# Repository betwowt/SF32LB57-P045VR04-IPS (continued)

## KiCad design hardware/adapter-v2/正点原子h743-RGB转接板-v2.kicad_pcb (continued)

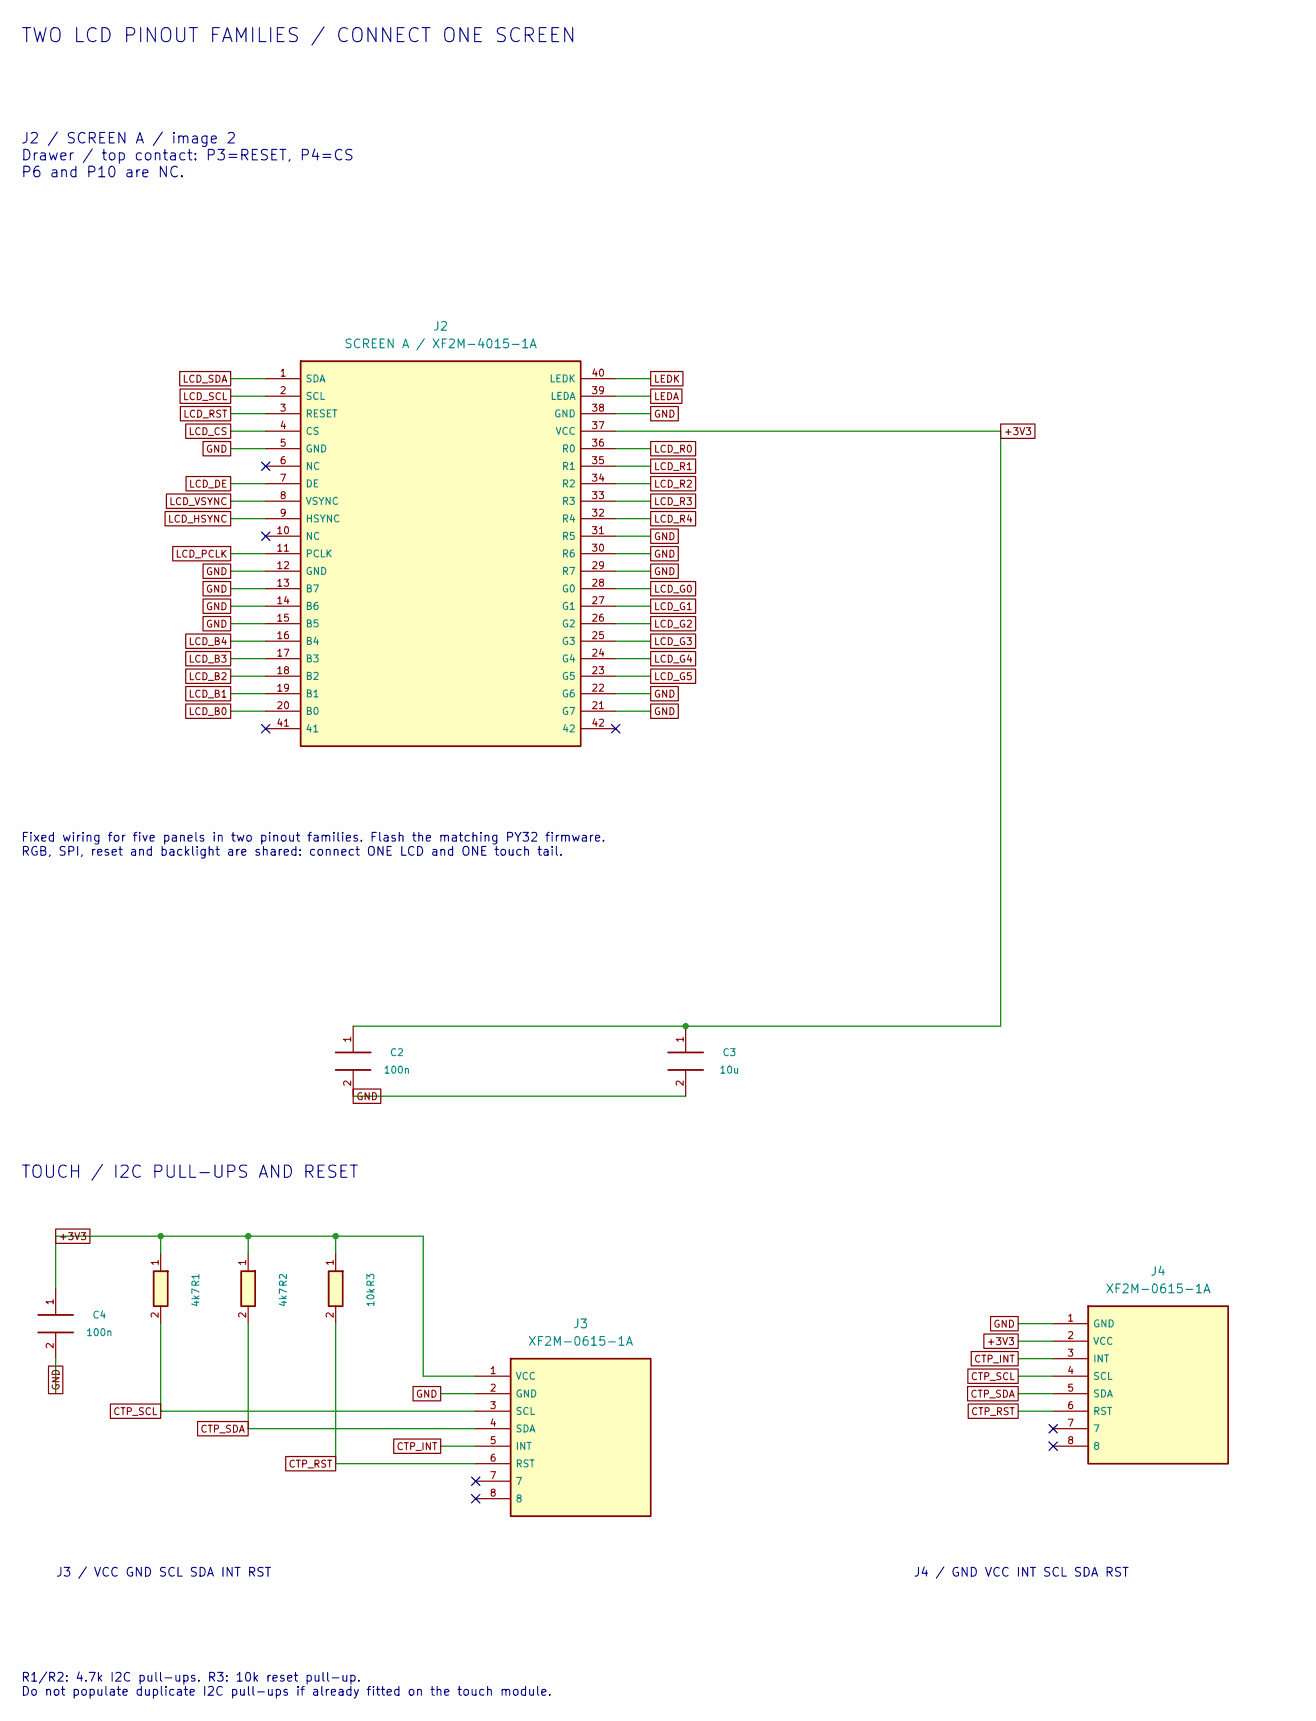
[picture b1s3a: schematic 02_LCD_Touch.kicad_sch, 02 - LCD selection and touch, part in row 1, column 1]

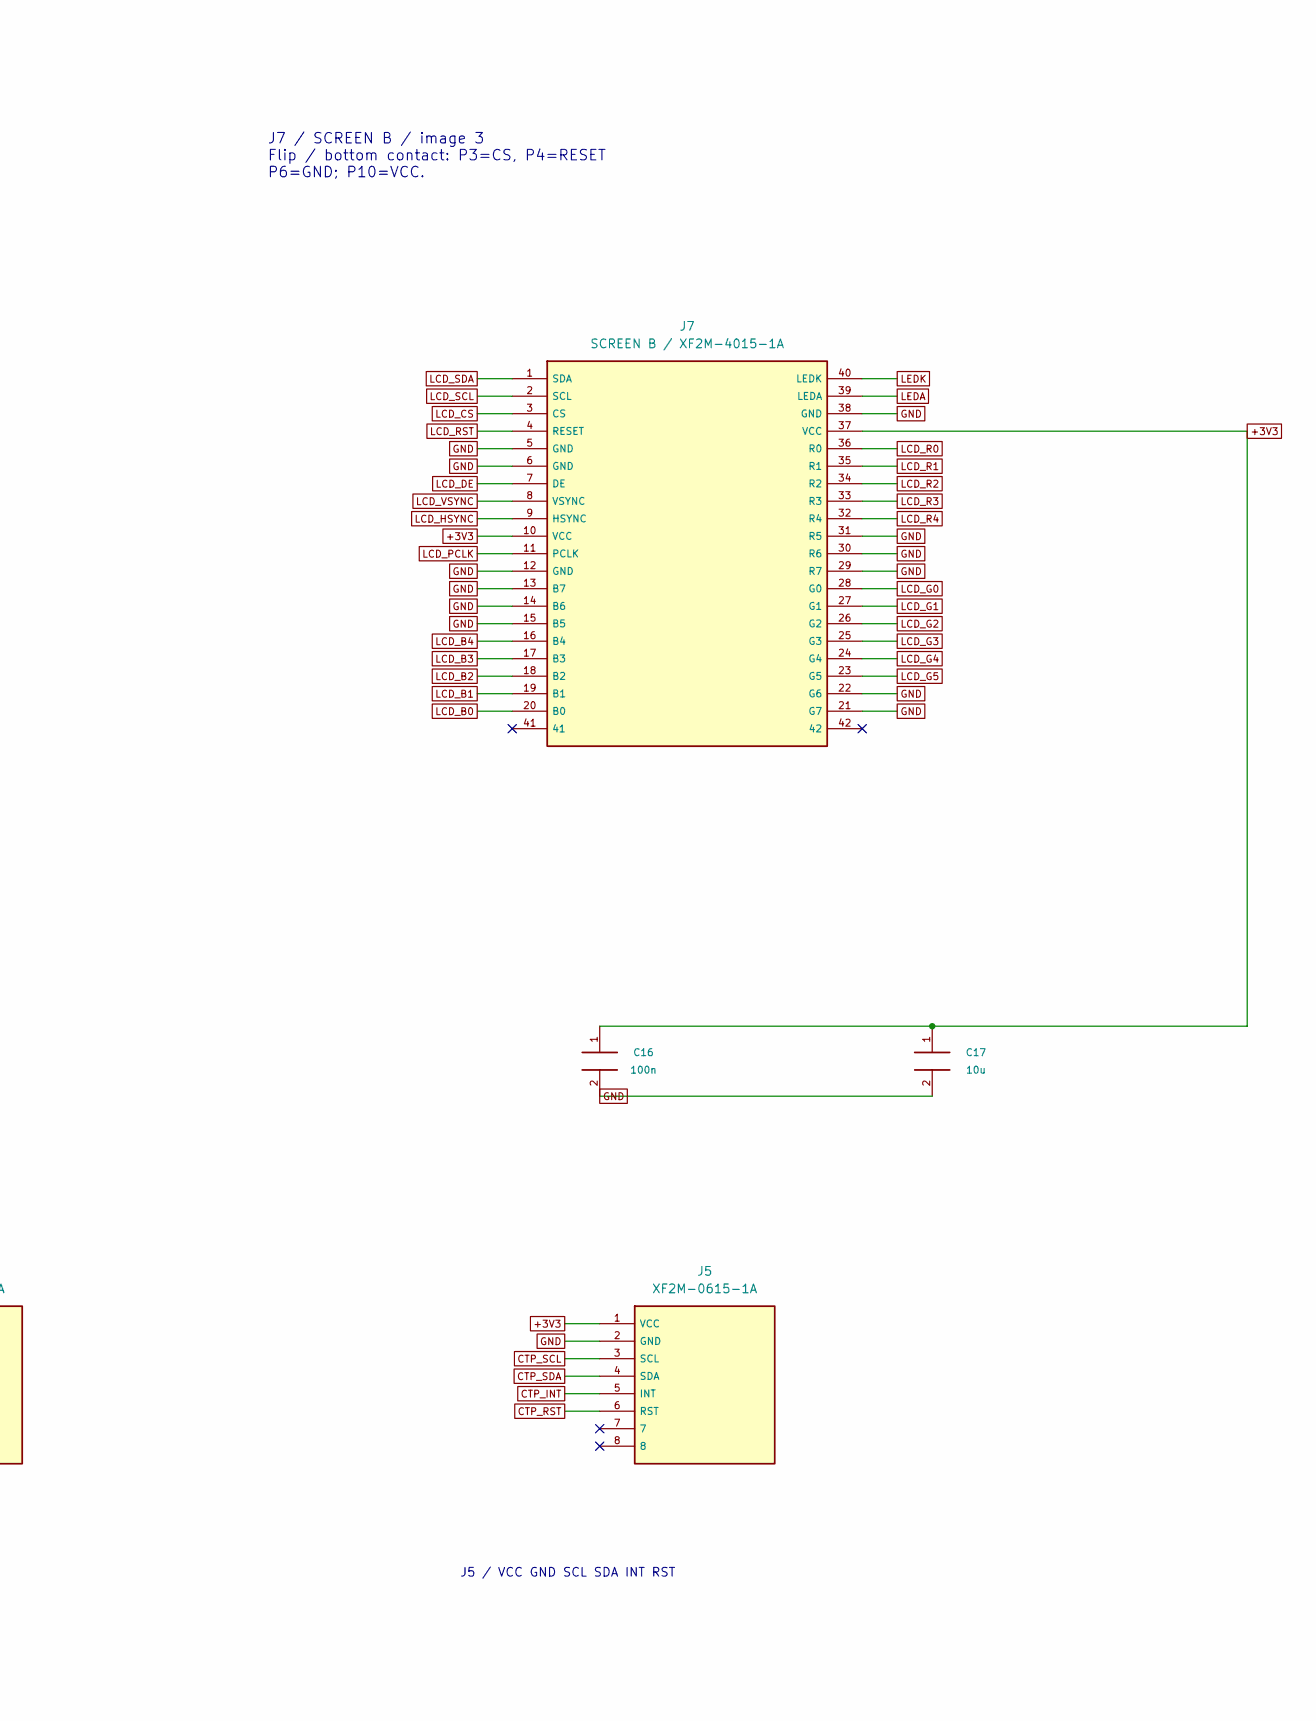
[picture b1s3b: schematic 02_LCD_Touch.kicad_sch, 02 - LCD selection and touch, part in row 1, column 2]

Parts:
C2, C4, C16: 100n; C_0603_1608Metric
C3, C17: 10u; C_0805_2012Metric
J2: SCREEN A / XF2M-4015-1A; FPC-SMD_P0.50-40P_LCS-SJ-H2.0
J3, J4, J5: XF2M-0615-1A; FPC-SMD_6P-P0.50_XUNPU_FPC-05F-6PH20
J7: SCREEN B / XF2M-4015-1A; FPC-SMD_AFC01-S40FCA-00
R1, R2: 4k7; R_0603_1608Metric
R3: 10k; R_0603_1608Metric

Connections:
+3V3: C2.1, C3.1, C4.1, C16.1, C17.1, J2.37 (VCC), J3.1 (VCC), J4.2 (VCC), J5.1 (VCC), J7.10 (VCC), J7.37 (VCC), R1.1, R2.1, R3.1; also elsewhere on the board
CTP_INT: J3.5 (INT), J4.3 (INT), J5.5 (INT); also elsewhere on the board
CTP_RST: J3.6 (RST), J4.6 (RST), J5.6 (RST), R3.2; also elsewhere on the board
CTP_SCL: J3.3 (SCL), J4.4 (SCL), J5.3 (SCL), R1.2; also elsewhere on the board
CTP_SDA: J3.4 (SDA), J4.5 (SDA), J5.4 (SDA), R2.2; also elsewhere on the board
GND: C2.2, C3.2, C4.2, C16.2, C17.2, J2.5 (GND), J2.12 (GND), J2.13 (B7), J2.14 (B6), J2.15 (B5), J2.21 (G7), J2.22 (G6), J2.29 (R7), J2.30 (R6), J2.31 (R5), J2.38 (GND), J3.2 (GND), J4.1 (GND), J5.2 (GND), J7.5 (GND), J7.6 (GND), J7.12 (GND), J7.13 (B7), J7.14 (B6), J7.15 (B5), J7.21 (G7), J7.22 (G6), J7.29 (R7), J7.30 (R6), J7.31 (R5), J7.38 (GND); also elsewhere on the board
LCD_B0: J2.20 (B0), J7.20 (B0); also elsewhere on the board
LCD_B1: J2.19 (B1), J7.19 (B1); also elsewhere on the board
LCD_B2: J2.18 (B2), J7.18 (B2); also elsewhere on the board
LCD_B3: J2.17 (B3), J7.17 (B3); also elsewhere on the board
LCD_B4: J2.16 (B4), J7.16 (B4); also elsewhere on the board
LCD_CS: J2.4 (CS), J7.3 (CS); also elsewhere on the board
LCD_DE: J2.7 (DE), J7.7 (DE); also elsewhere on the board
LCD_G0: J2.28 (G0), J7.28 (G0); also elsewhere on the board
LCD_G1: J2.27 (G1), J7.27 (G1); also elsewhere on the board
LCD_G2: J2.26 (G2), J7.26 (G2); also elsewhere on the board
LCD_G3: J2.25 (G3), J7.25 (G3); also elsewhere on the board
LCD_G4: J2.24 (G4), J7.24 (G4); also elsewhere on the board
LCD_G5: J2.23 (G5), J7.23 (G5); also elsewhere on the board
LCD_HSYNC: J2.9 (HSYNC), J7.9 (HSYNC); also elsewhere on the board
LCD_PCLK: J2.11 (PCLK), J7.11 (PCLK); also elsewhere on the board
LCD_R0: J2.36 (R0), J7.36 (R0); also elsewhere on the board
LCD_R1: J2.35 (R1), J7.35 (R1); also elsewhere on the board
LCD_R2: J2.34 (R2), J7.34 (R2); also elsewhere on the board
LCD_R3: J2.33 (R3), J7.33 (R3); also elsewhere on the board
LCD_R4: J2.32 (R4), J7.32 (R4); also elsewhere on the board
LCD_RST: J2.3 (RESET), J7.4 (RESET); also elsewhere on the board
LCD_SCL: J2.2 (SCL), J7.2 (SCL); also elsewhere on the board
LCD_SDA: J2.1 (SDA), J7.1 (SDA); also elsewhere on the board
LCD_VSYNC: J2.8 (VSYNC), J7.8 (VSYNC); also elsewhere on the board
LEDA: J2.39 (LEDA), J7.39 (LEDA); also elsewhere on the board
LEDK: J2.40 (LEDK), J7.40 (LEDK); also elsewhere on the board

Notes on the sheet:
J4 / GND VCC INT SCL SDA RST
J7 / SCREEN B / image 3 Flip / bottom contact: P3=CS, P4=RESET P6=GND; P10=VCC.
J3 / VCC GND SCL SDA INT RST
TWO LCD PINOUT FAMILIES / CONNECT ONE SCREEN
Fixed wiring for five panels in two pinout families. Flash the matching PY32 firmware. RGB, SPI, reset and backlight are shared: connect ONE LCD and ONE touch tail.
R1/R2: 4.7k I2C pull-ups. R3: 10k reset pull-up. Do not populate duplicate I2C pull-ups if already fitted on the touch module.
J2 / SCREEN A / image 2 Drawer / top contact: P3=RESET, P4=CS P6 and P10 are NC.
J5 / VCC GND SCL SDA INT RST
TOUCH / I2C PULL-UPS AND RESET

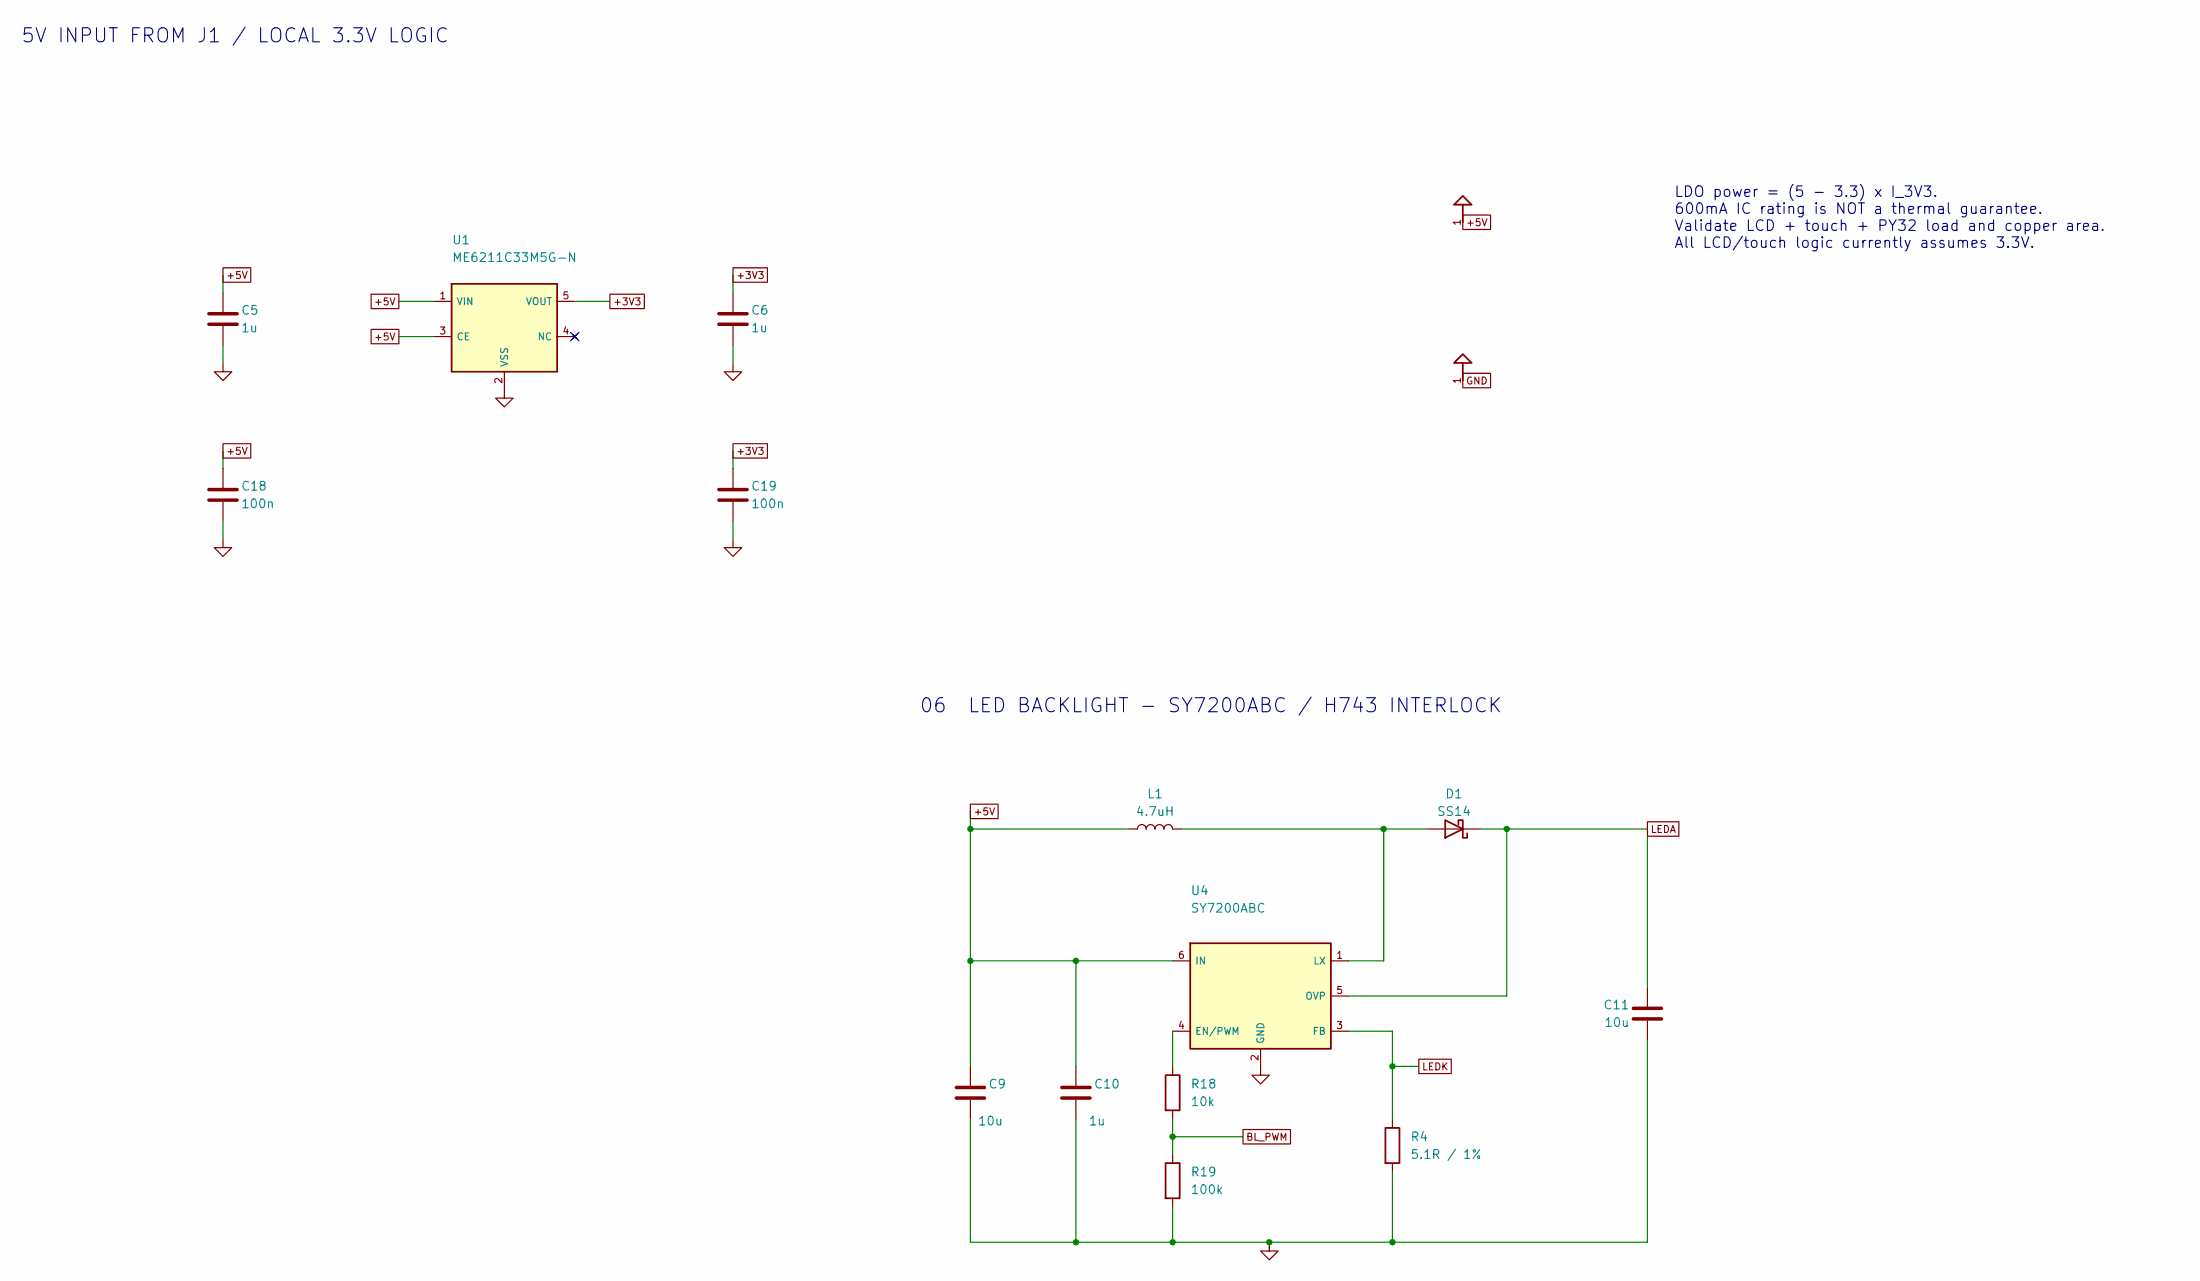
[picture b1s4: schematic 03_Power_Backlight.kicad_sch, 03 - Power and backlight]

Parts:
C5, C6, C10: 1u; C_0805_2012Metric
C9, C11: 10u; C_0805_2012Metric
C18, C19: 100n; C_0603_1608Metric
D1: SS14; D_SMA
L1: 4.7uH; L_T113_2.5x2.0; LCSC Part C5832360
R4: 5.1R / 1%; R_0603_1608Metric
R18: 10k; R_0603_1608Metric
R19: 100k; R_0603_1608Metric
U1: ME6211C33M5G-N; SOT-23-5
U4: SY7200ABC; SOT-23-6

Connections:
+3V3: C6.1, C19.1, U1.5 (VOUT); also elsewhere on the board
+5V: C5.1, C9.1, C10.1, C18.1, L1.1, U1.1 (VIN), U1.3 (CE), U4.6 (IN); also elsewhere on the board
BL_PWM: R18.2, R19.1; also elsewhere on the board
GND: C5.2, C6.2, C9.2, C10.2, C11.2, C18.2, C19.2, R4.2, R19.2, U1.2 (VSS), U4.2 (GND); also elsewhere on the board
LEDA: C11.1, D1.1 (K), U4.5 (OVP); also elsewhere on the board
LEDK: R4.1, U4.3 (FB); also elsewhere on the board
unnamed: D1.2 (A), L1.2, U4.1 (LX)
unnamed: R18.1, U4.4 (EN/PWM)

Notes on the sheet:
LDO power = (5 - 3.3) x I_3V3. 600mA IC rating is NOT a thermal guarantee. Validate LCD + touch + PY32 load and copper area. All LCD/touch logic currently assumes 3.3V.
5V INPUT FROM J1 / LOCAL 3.3V LOGIC
06 LED BACKLIGHT - SY7200ABC / H743 INTERLOCK

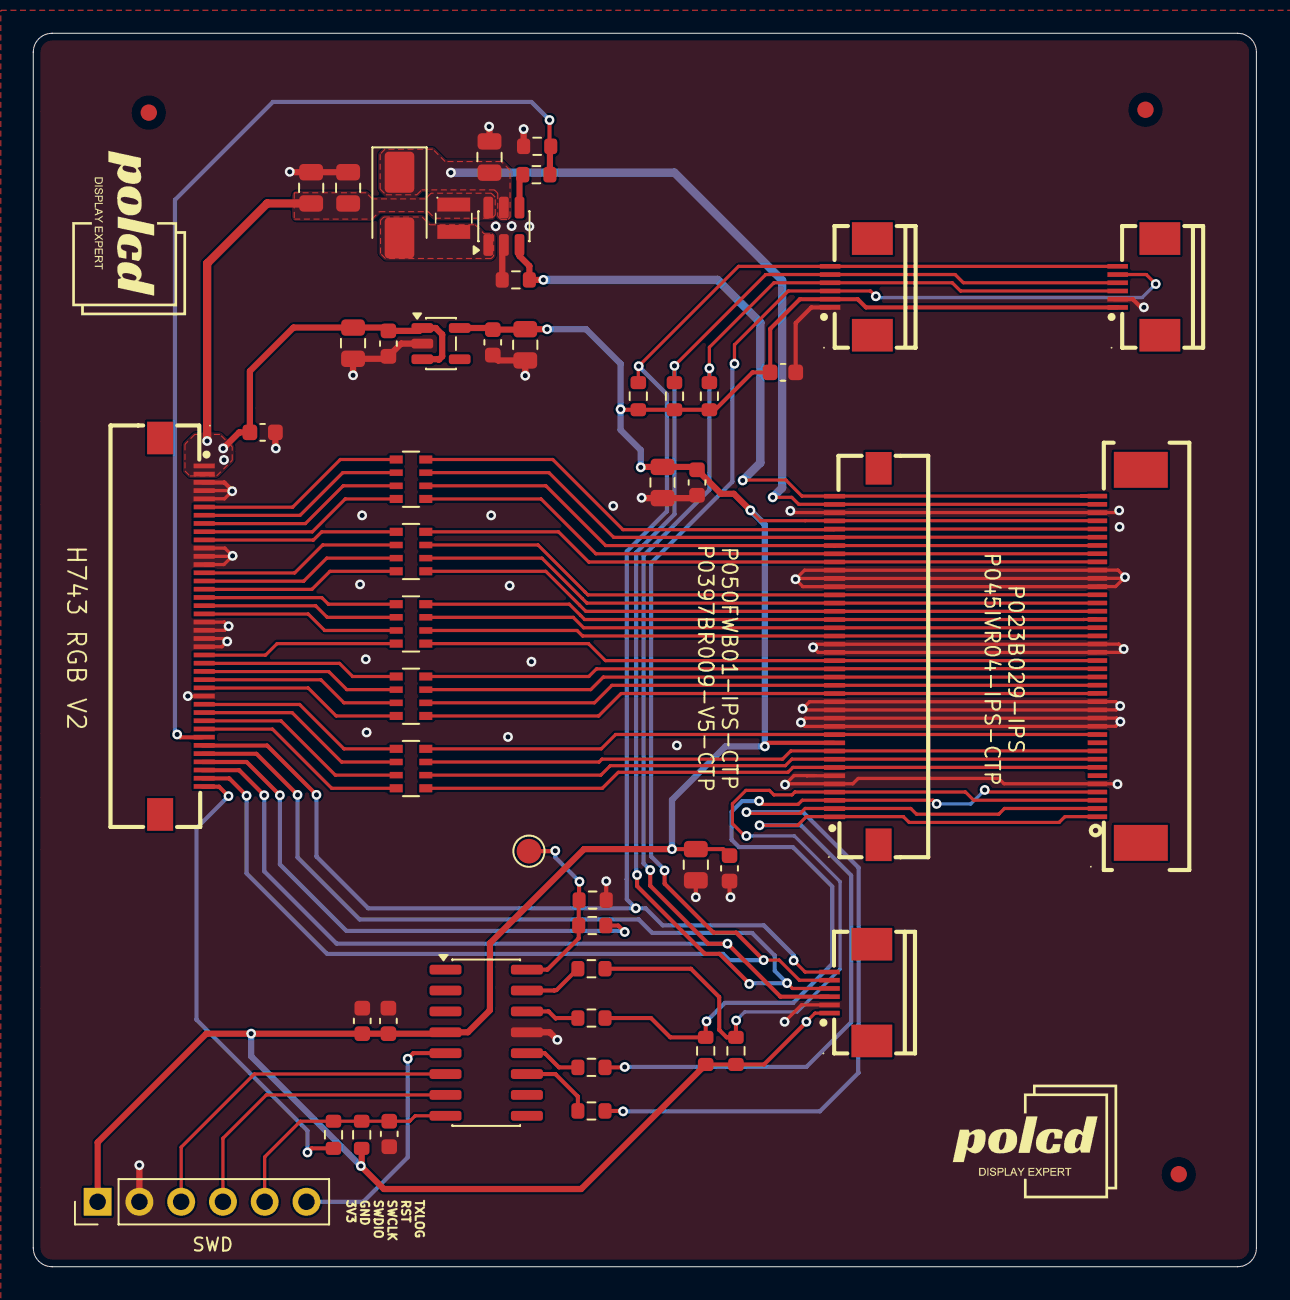
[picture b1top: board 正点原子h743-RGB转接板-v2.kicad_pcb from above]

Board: 2 copper layers, 74.4 x 75.0 mm, 53 parts (0 on the bottom side), 67 nets.

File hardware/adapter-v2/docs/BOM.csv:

Reference,Value,Footprint,DNP,Design_note,Datasheet
J1,H743 / XF2M-4015-1A,Adapter:Omron_XF2M_40,False,40pin 0.5mm confirmed by user. Verify pin1-to-pin1 continuity; two MP pads are ground.,
RN1,33R x4 / CAY16-330J4LF,Adapter:R_Array4_0603,False,"4 isolated elements, never commoned. Initial 33R; adapter-side series link is not ideal source termination for long FFC.",https://www.bourns.com/docs/Product-Datasheets/CATCAY.pdf
RN2,33R x4 / CAY16-330J4LF,Adapter:R_Array4_0603,False,"4 isolated elements, never commoned. Initial 33R; adapter-side series link is not ideal source termination for long FFC.",https://www.bourns.com/docs/Product-Datasheets/CATCAY.pdf
RN3,33R x4 / CAY16-330J4LF,Adapter:R_Array4_0603,False,"4 isolated elements, never commoned. Initial 33R; adapter-side series link is not ideal source termination for long FFC.",https://www.bourns.com/docs/Product-Datasheets/CATCAY.pdf
RN4,33R x4 / CAY16-330J4LF,Adapter:R_Array4_0603,False,"4 isolated elements, never commoned. Initial 33R; adapter-side series link is not ideal source termination for long FFC.",https://www.bourns.com/docs/Product-Datasheets/CATCAY.pdf
RN5,33R x4 / CAY16-330J4LF,Adapter:R_Array4_0603,False,"4 isolated elements, never commoned. Initial 33R; adapter-side series link is not ideal source termination for long FFC.",https://www.bourns.com/docs/Product-Datasheets/CATCAY.pdf
C1,100n / 16V,Adapter:C_0603,False,,
J2,SCREEN A / XF2M-4015-1A,Adapter:Omron_XF2M_40,False,"Dedicated image2 pinout, pins6/10 NC. Candidate dual-contact seat supports top-contact tail; confirm 0.3+/-0.05mm thickness and pin1.",
J7,SCREEN B / XF2M-4015-1A,Adapter:Omron_XF2M_40,False,"Dedicated image3 pinout, pin6 GND and pin10 3V3. Candidate dual-contact seat supports bottom-contact tail; confirm 0.3+/-0.05mm thickness and pin1.",
C2,100n / 10V,Adapter:C_0603,False,,
C3,10u / 10V,Adapter:C_0805,False,,
C16,100n / 10V,Adapter:C_0603,False,,
C17,10u / 10V,Adapter:C_0805,False,,
J3,XF2M-0615-1A,Adapter:Omron_XF2M_6,False,0.5mm/0.3mm candidate; confirm actual touch tail dimensions/contact direction. Only one of J3/J4/J5 may be used.,
J4,XF2M-0615-1A,Adapter:Omron_XF2M_6,False,0.5mm/0.3mm candidate; confirm actual touch tail dimensions/contact direction. Only one of J3/J4/J5 may be used.,
J5,XF2M-0615-1A,Adapter:Omron_XF2M_6,False,0.5mm/0.3mm candidate; confirm actual touch tail dimensions/contact direction. Only one of J3/J4/J5 may be used.,
R1,4k7,Adapter:R_0603,False,DNP if equivalent pullups already fitted on touch module.,
R2,4k7,Adapter:R_0603,False,DNP if equivalent pullups already fitted on touch module.,
R3,10k,Adapter:R_0603,False,,
C4,100n / 10V,Adapter:C_0603,False,,
U1,AP2112K-3.3TRG1,Adapter:SOT23_5,False,,https://www.diodes.com/datasheet/download/AP2112.pdf
C5,10u / 16V,Adapter:C_0805,False,,
C6,100n / 16V,Adapter:C_0603,False,,
C7,10u / 10V,Adapter:C_0805,False,,
C8,100n / 10V,Adapter:C_0603,False,,
L1,4.7uH,Adapter:L_T113_2.5x2.0,False,"T113_MIPI_Adapter placement/footprint; selected 4.7uH part, verify Isat, DCR and thermal.",
D1,SS14,Adapter:D_SMA,False,,
U2,SY7200ABC,Adapter:SOT23_6,False,,https://www.silergy.com/download/downloadFile?ftype=note&id=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
C9,10uF / 50V,Adapter:C_0805,False,,
C10,1uF / 50V,Adapter:C_0805,False,,
C11,10uF / 50V,Adapter:C_0805,False,"T113 backlight output capacitor; 50V X7R, account for DC bias.",
R4,5R1 / 1%,Adapter:R_0603,False,Feedback value retained at 5.1 ohm / 1%; only the T113 0603 body and placement are adopted.,
U4,SN74LVC1G08DBVR,Adapter:SOT23_5,False,,https://www.ti.com/lit/ds/symlink/sn74lvc1g08.pdf
R5,10k,Adapter:R_0603,False,,
R6,100k,Adapter:R_0603,False,,
R7,100k,Adapter:R_0603,False,,
C12,100n / 10V,Adapter:C_0603,False,,
U3,PY32F002AW15S / SOP16,Adapter:SOIC16,False,Select exact PY32F002AW15S orderable suffix. Other PY32F002 variants/packages have different pinouts.,https://www.puyasemi.com/download_path/%E6%95%B0%E6%8D%AE%E6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
R8,100R,Adapter:R_0603,False,,
R9,100R,Adapter:R_0603,False,,
R10,100R,Adapter:R_0603,False,,
R11,100R,Adapter:R_0603,False,,
R12,10k,Adapter:R_0603,False,,
R13,10k,Adapter:R_0603,False,,
R14,100k,Adapter:R_0603,False,,
R15,1k,Adapter:R_0603,False,PG3 on host must be INPUT; provides init-ready handshake.,
R16,0R,Adapter:R_0603,False,Host reset link. DNP for isolated MCU debugging; confirm host RESET is 3.3V domain.,
R17,10k,Adapter:R_0603,False,,
C13,100n / 10V,Adapter:C_0603,False,,
C14,100n / 10V,Adapter:C_0603,False,,
C15,1u / 10V,Adapter:C_0603,False,,
J6,PY32 SWD / 2.54mm,Adapter:Header1x06,False,VTREF is a reference output; do not back-power through debugger. PA9 debug UART is firmware-dependent.,
TP1,+5V,Adapter:TestPoint,False,,
TP2,+3V3,Adapter:TestPoint,False,,
TP3,GND,Adapter:TestPoint,False,,
TP4,LCD_READY,Adapter:TestPoint,False,,

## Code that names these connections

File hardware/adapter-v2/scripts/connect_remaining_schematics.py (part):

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    p.text('RGB565 / 20 SERIES CHANNELS',266.7,40.64,1.778)
    p.text('RN1..RN4: R3..R7, G2..G7, B3..B7\nRN5: PCLK / HSYNC / VSYNC / DE\nFour isolated 33R elements per package.\n\nPlace near J1. Tune resistance with the real cable.\nLCD unused low bits are held at GND.\nUse one LCD socket and one touch socket.',266.7,50.8)
    p.text('HOST CONTROL SIGNALS',266.7,93.98,1.778)
    p.text('PH6: software I2C SCL; PI3: software I2C SDA\nPH7: touch INT; PI8: touch RESET\nPG3: PY32 READY input; PB5: backlight PWM\nHost RESET links to PY32 NRST through R16.',266.7,104.14)
    p.text('40-pin / 0.5mm. Verify actual cable pin-1 continuity before assembly.',15.24,228.6)
    p.finish()

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def mcu_page():
    p=Page('04_PY32_Init')
    p.text('PY32F002A / SOFTWARE SPI INITIALIZER / 3.3V',15.24,15.24,2.032)
    for i,(r,pin,y,net) in enumerate([('R8','11',27.94,'PY_LCD_SCK'),('R9','12',43.18,'PY_LCD_SDA'),('R10','14',58.42,'PY_LCD_CS'),('R11','15',73.66,'PY_LCD_RST')]):
        p.move(r,203.2,y); p.use(r,'1','2'); p.use('U3',pin)
        a=p.pos('U3',pin); bend=139.7+i*10.16
        p.wire(a,(bend,a[1]),(bend,y),p.pos(r,'1'))
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    p.use('R16','2'); p.use('R17','2'); p.use('C13','1'); p.use('U3','8')
    p.wire(p.pos('U3','8'),(55.88,64.77),(55.88,116.84),p.pos('C13','1'))
    p.wire(p.pos('R17','2'),(76.2,116.84)); p.dot((76.2,116.84))
    p.label('PY_NRST',(91.44,116.84),local=True)
    # Local MCU supply rail and its capacitor pair.
    for r,x in [('C14',25.4),('C15',43.18)]:
        p.move(r,x,48.26); p.use(r,'1','2')
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    p.use('U3','16'); p.use('R14','1'); p.use('R15','1')
    p.wire(p.pos('U3','16'),(132.08,69.85),(132.08,152.4),p.pos('R15','1'))
    p.wire(p.pos('R14','1'),(160.02,152.4)); p.dot((160.02,152.4))
    p.label('LCD_READY',(172.72,152.4),local=True)
    p.text('RESET / R16 links host reset to PY32',20.32,88.9)
    p.text('READY TO HOST + BACKLIGHT GATE',139.7,137.16,1.524)
    p.text('SWD PROGRAMMING',20.32,168.91,1.524)
    p.text('No jumpers; manually flash the selected panel firmware.\nPA0=SCK, PA1=SDA, PA2=CS, PA3=RESET.\nKeep PA13/PA14 available for SWD programming.',312.42,38.1)
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    p.text('R14 keeps READY low during reset.\nR15 isolates the host READY input.',139.7,185.42)
    p.finish()
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
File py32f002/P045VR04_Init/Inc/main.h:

/**
  ******************************************************************************
  * @file    main.h
  * @brief   P045VR04-IPS 屏幕初始化(PY32F002AW15S6TU) 头文件
  * @note    硬件: H743_RGB_Adapter 转接板 "04 - PY32 display initialization"
  *
  *          PY32管脚分配(与转接板原理图一致):
  *            PA0  LCD_SCK   : ST7701S 3线SPI时钟   (经R8  100R)
  *            PA1  LCD_SDA   : ST7701S 3线SPI数据   (经R9  100R)
  *            PA2  LCD_CS    : ST7701S 3线SPI片选   (经R10 100R)
  *            PA3  LCD_RST   : 面板复位             (经R11 100R, 上拉R13 10k)
  *            PA6  READY     : 输出给H743(PG3), 初始化完成前为低
  *            PA9  TX_LOG    : USART1_TX 调试日志(115200-8-N-1)
  *            PA13/PA14      : SWDIO/SWCLK, 保留给SWD下载(不做任何配置)
  *
  *          固件流程(对应原理图"FIRMWARE SEQUENCE"):
  *            1. READY=0; CS=1; SCL/SDA为3线SPI空闲电平(低);
  *            2. 等待电源稳定, 复位面板;
  *            3. 发送面板初始化表(3线SPI, 9bit);
  *            4. 等待所有延时, 置READY=1;
  *            5. H743检测到PG3为高后才打开背光.
  ******************************************************************************
  */

#ifndef __MAIN_H
#define __MAIN_H

#ifdef __cplusplus
extern "C" {
#endif

/* Includes ------------------------------------------------------------------*/
#include "py32f0xx_hal.h"
#include "panel_st7701.h"

/* Private defines -----------------------------------------------------------*/
/* 面板3线SPI/复位/READY引脚(全部在GPIOA)
 * 转接板上PY32固定接到4个网络(原理图04_PY32_Init, 各串100R; 屏座J2/J7只把这4个网络
 * 引到第1~4脚):
 *   PA0 -> LCD_SCL   R8  100R              (J2.2 / J7.2)
 *   PA1 -> LCD_SDA   R9  100R              (J2.1 / J7.1)
 *   PA2 -> LCD_CS    R10 100R              (J2.4 / J7.3)
 *   PA3 -> LCD_RST   R11 100R(R13 10k上拉) (J2.3 / J7.4)
 * 不同屏的这4个信号在FPC上的位置/顺序不同, 必须先用万用表通断实测(屏脚 -> PY32脚),
 * 再选下面的映射. 只能在PA0/PA1/PA2/PA3之间置换;
 * PA6=READY, PA9=TX_LOG, PA13/PA14=SWD 不可改.
 *
 *   PANEL_MAP_P045VR04 : 本屏实测(直插J2): 屏SCL=PA0, 屏SDA=PA3, 屏CS=PA1, 屏RESET=PA2  ←默认
 *   PANEL_MAP_STD      : 与转接板网络名1:1: PA0=SCL, PA1=SDA, PA2=CS, PA3=RESET
 *   PANEL_MAP_CUSTOM   : 实测任意置换, 填下面 PANEL_CUSTOM_xxx 四行
 */
#define PANEL_MAP_P045VR04              1
#define PANEL_MAP_STD                   0
#define PANEL_MAP_CUSTOM                9

#ifndef PANEL_MAP
#define PANEL_MAP                       PANEL_MAP_P045VR04
#endif

#define LCD_PANEL_PORT          GPIOA

#if   (PANEL_MAP == PANEL_MAP_P045VR04)
  #define LCD_SCK_PIN           GPIO_PIN_0          /* 屏SCL   -> PA0 */
  #define LCD_SDA_PIN           GPIO_PIN_3          /* 屏SDA   -> PA3 */
  #define LCD_CS_PIN            GPIO_PIN_1          /* 屏CS    -> PA1 */
  #define LCD_RST_PIN           GPIO_PIN_2          /* 屏RESET -> PA2 */
#elif (PANEL_MAP == PANEL_MAP_STD)
  #define LCD_SCK_PIN           GPIO_PIN_0          /* 屏SCL   -> PA0 */
  #define LCD_SDA_PIN           GPIO_PIN_1          /* 屏SDA   -> PA1 */
  #define LCD_CS_PIN            GPIO_PIN_2          /* 屏CS    -> PA2 */
  #define LCD_RST_PIN           GPIO_PIN_3          /* 屏RESET -> PA3 */
#elif (PANEL_MAP == PANEL_MAP_CUSTOM)
  #define PANEL_CUSTOM_SCL      GPIO_PIN_0          /* 屏SCL  实测接到的PY32引脚 */
  #define PANEL_CUSTOM_SDA      GPIO_PIN_1          /* 屏SDA  实测接到的PY32引脚 */
  #define PANEL_CUSTOM_CS       GPIO_PIN_2          /* 屏CS   实测接到的PY32引脚 */
  #define PANEL_CUSTOM_RST      GPIO_PIN_3          /* 屏RESET实测接到的PY32引脚 */
  #define LCD_SCK_PIN           PANEL_CUSTOM_SCL
  #define LCD_SDA_PIN           PANEL_CUSTOM_SDA
  #define LCD_CS_PIN            PANEL_CUSTOM_CS
  #define LCD_RST_PIN           PANEL_CUSTOM_RST
#else
  #error "PANEL_MAP value is invalid (see Inc/main.h)"
#endif

#define LCD_READY_PIN           GPIO_PIN_6          /* H743的PG3输入 */

/* 日志串口(UART1 TX) */
#define LOG_UART                USART1
#define LOG_UART_PORT           GPIOA
#define LOG_TX_PIN              GPIO_PIN_9
#define LOG_TX_AF               GPIO_AF1_USART1

/* Private function prototypes -----------------------------------------------*/
void APP_ErrorHandler(void);
void app_log(const char *str);

#ifdef __cplusplus
}
#endif

#endif /* __MAIN_H */
